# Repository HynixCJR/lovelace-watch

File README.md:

# lovelace watch

this is the repo for lovelace, a smart-ish watch in a thin, compact body. it has:

- four 3x5 led matrices to display the time
- 28 argb leds along the ring of the watch (for flashlight and notification purposes)
- bluetooth 6.0 connection to a smartphone 
- lra vibration motor for notifications
- step tracking
- raise to wake
- auto brightness
- compass
- usb-c charging

this repo currently houses the pcb for the watch.

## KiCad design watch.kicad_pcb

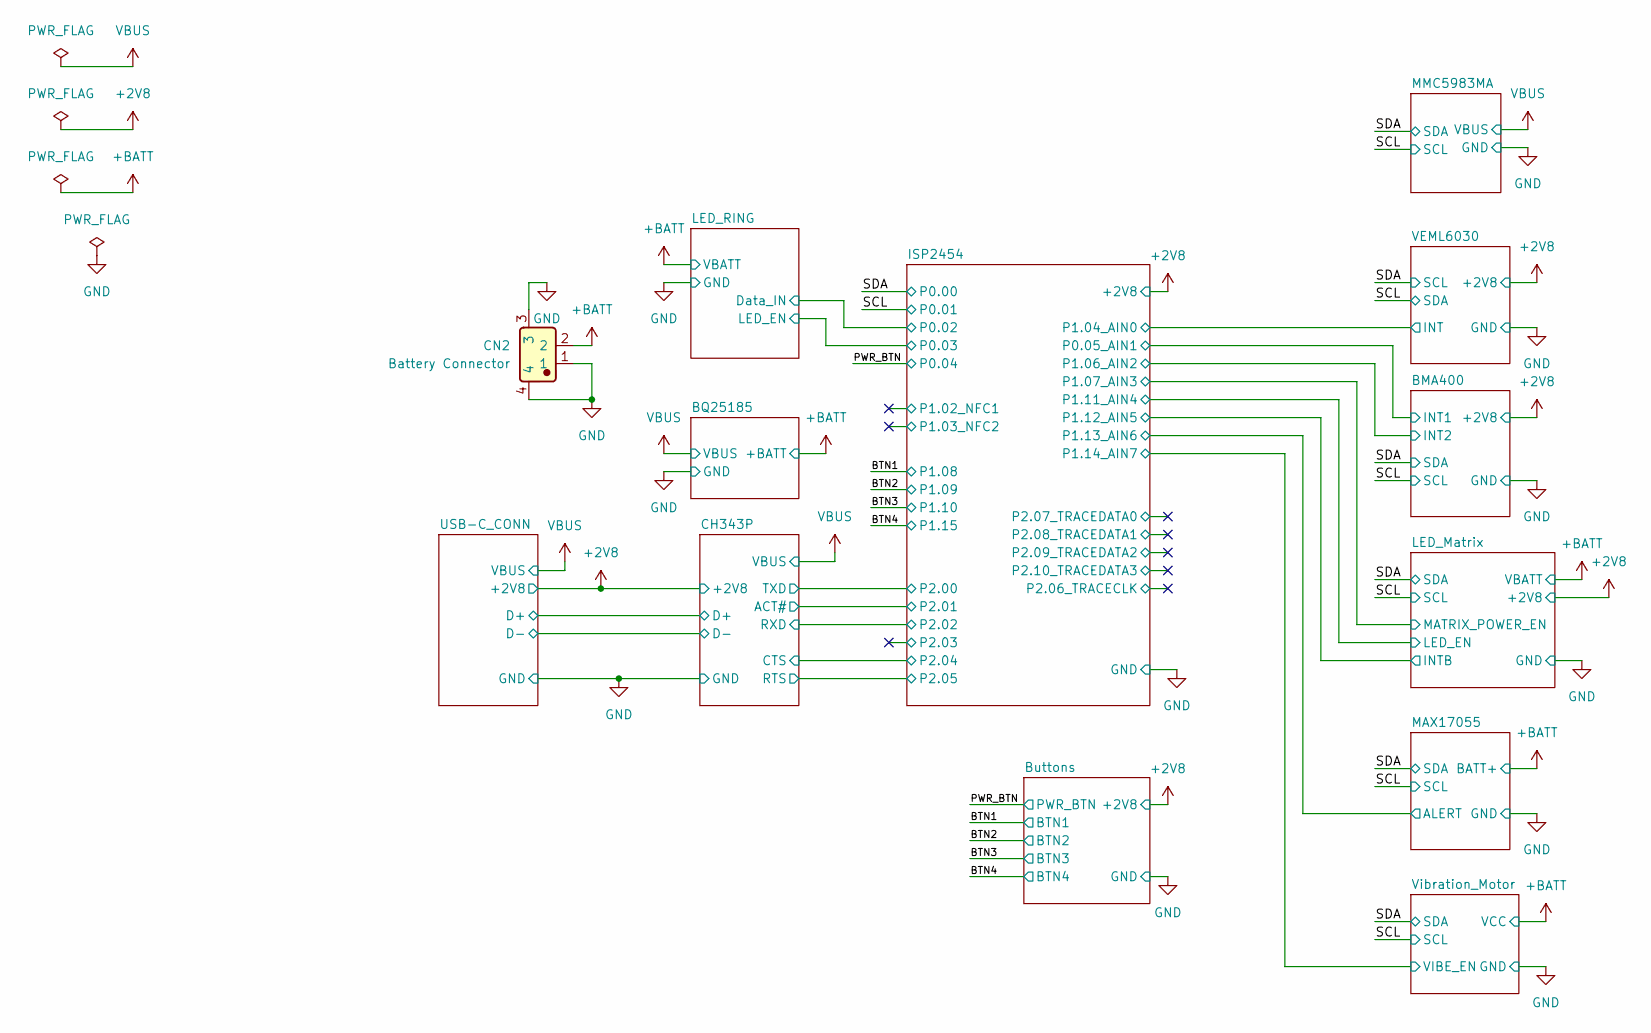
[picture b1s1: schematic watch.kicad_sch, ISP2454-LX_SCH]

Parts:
CN2: Battery Connector; 7900-02A4-TG; Manufacturer Part 7900-02A4-TG; LCSC C53403918

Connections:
+BATT: CN2.2; also elsewhere on the board
GND: CN2.1, CN2.3, CN2.4; also elsewhere on the board

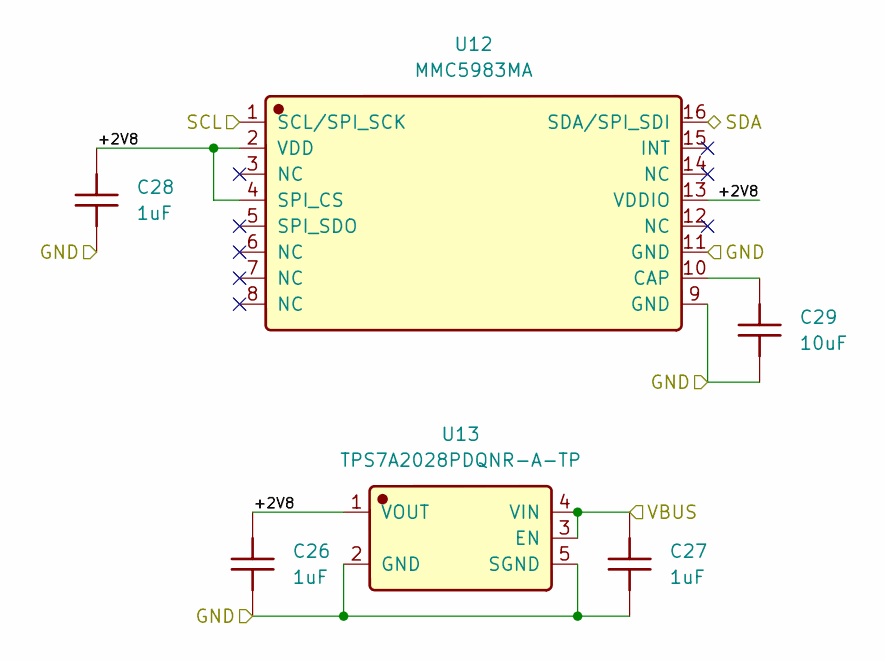
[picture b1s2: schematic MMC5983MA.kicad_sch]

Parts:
C26, C27, C28: 1uF; C_0402_1005Metric; Manufacturer Part 2F01MC105B2K5D0; LCSC C54824955
C29: 10uF; C_0603_1608Metric; Manufacturer Part CL10A106MQ8NNNC; LCSC C1691
U12: MMC5983MA; LGA-16_3x3mm_P0.5mm; Manufacturer Part MMC5983MA; LCSC C404329
U13: TPS7A2028PDQNR-A-TP; UDFN-4-1EP_1x1mm_P0.65mm_EP0.48x0.48mm; Manufacturer Part TPS7A2028PDQNR-A-TP; LCSC C55191366

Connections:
/MMC5983MA/+2V8: C26.2, C28.2, U12.2 (VDD), U12.4 (SPI_CS), U12.13 (VDDIO), U13.1 (VOUT)
/SCL: U12.1 (SCL/SPI_SCK); also elsewhere on the board
/SDA: U12.16 (SDA/SPI_SDI); also elsewhere on the board
GND: C26.1, C27.1, C28.1, C29.1, U12.9 (GND), U12.11 (GND), U13.2 (GND), U13.5 (SGND); also elsewhere on the board
unnamed: C29.2, U12.10 (CAP)
VBUS: C27.2, U13.3 (EN), U13.4 (VIN); also elsewhere on the board

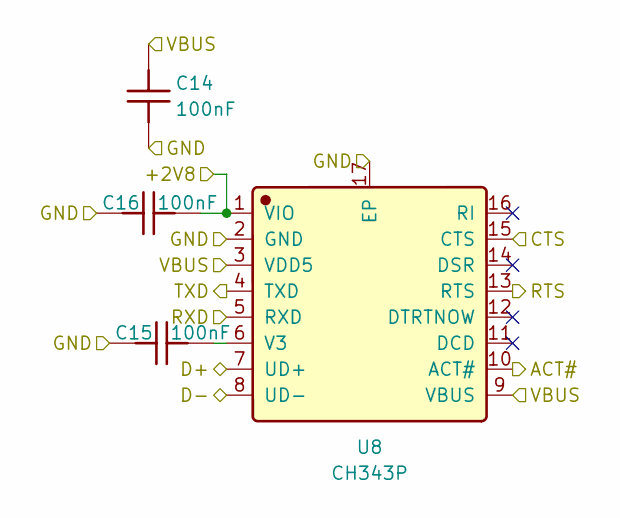
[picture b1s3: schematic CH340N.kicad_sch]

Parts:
C14, C15, C16: 100nF; C_0402_1005Metric; Manufacturer Part 2F01MC104X2K7D0; LCSC C54824947
U8: CH343P; TQFN-16-1EP_3x3mm_P0.5mm_EP1.6x1.6mm; Manufacturer Part CH343P; LCSC C2846043

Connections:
+2V8: C16.1, U8.1 (VIO); also elsewhere on the board
/CH343P/ACT#: U8.10 (ACT#); also elsewhere on the board
/CH343P/CTS: U8.15 (CTS); also elsewhere on the board
/CH343P/D+: U8.7 (UD+); also elsewhere on the board
/CH343P/D-: U8.8 (UD-); also elsewhere on the board
/CH343P/RTS: U8.13 (RTS); also elsewhere on the board
/CH343P/RXD: U8.5 (RXD); also elsewhere on the board
/CH343P/TXD: U8.4 (TXD); also elsewhere on the board
GND: C14.1, C15.2, C16.2, U8.2 (GND), U8.17 (EP); also elsewhere on the board
unnamed: C15.1, U8.6 (V3)
VBUS: C14.2, U8.3 (VDD5), U8.9 (VBUS); also elsewhere on the board

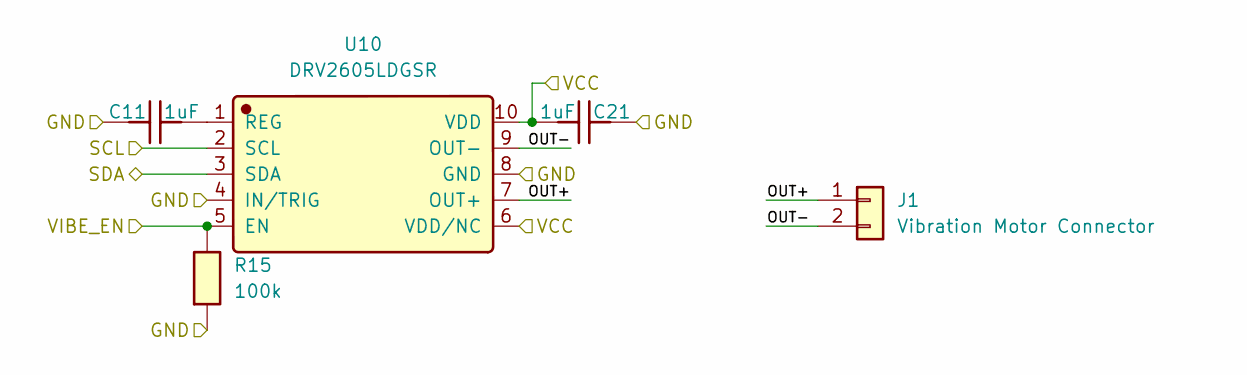
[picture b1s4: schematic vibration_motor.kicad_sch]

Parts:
C11, C21: 1uF; C_0402_1005Metric; Manufacturer Part 2F01MC105B2K5D0; LCSC C54824955
J1: Vibration Motor Connector; Molex_KK-254_AE-6410-02A_1x02_P2.54mm_Vertical
R15: 100k; R_0402_1005Metric; Manufacturer Part HRC0402J104 DNTO; LCSC C54920715
U10: DRV2605LDGSR; MSOP-10_3x3mm_P0.5mm; Manufacturer Part DRV2605LDGSR; LCSC C527464

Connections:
+BATT: C21.1, U10.6 (VDD/NC), U10.10 (VDD); also elsewhere on the board
/ISP2454/P1.14_AIN7: R15.2, U10.5 (EN); also elsewhere on the board
/SCL: U10.2 (SCL); also elsewhere on the board
/SDA: U10.3 (SDA); also elsewhere on the board
/Vibration_Motor/OUT+: J1.1, U10.7 (OUT+)
/Vibration_Motor/OUT-: J1.2, U10.9 (OUT-)
GND: C11.2, C21.2, R15.1, U10.4 (IN/TRIG), U10.8 (GND); also elsewhere on the board
unnamed: C11.1, U10.1 (REG)

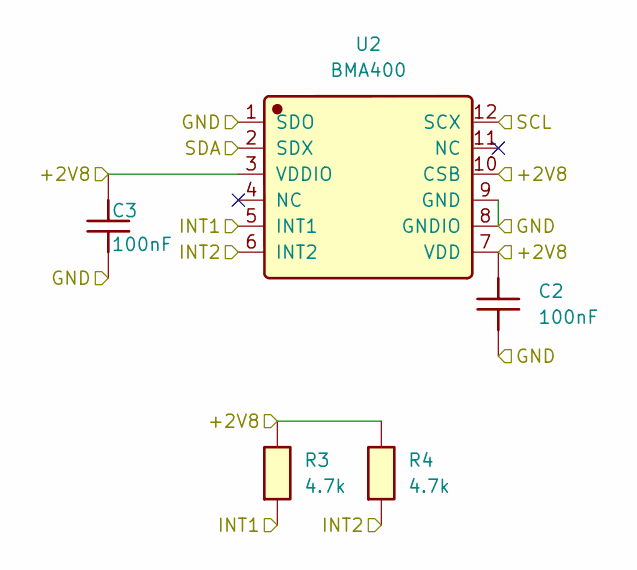
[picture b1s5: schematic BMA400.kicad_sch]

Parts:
C2, C3: 100nF; C_0402_1005Metric; Manufacturer Part 2F01MC104X2K7D0; LCSC C54824947
R3, R4: 4.7k; R_0402_1005Metric; Manufacturer Part RCA024K7JLF; LCSC C22369185
U2: BMA400; LGA-12_2x2mm_P0.5mm; Manufacturer Part BMA400; LCSC C437655

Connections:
+2V8: C2.2, C3.2, R3.2, R4.2, U2.3 (VDDIO), U2.7 (VDD), U2.10 (CSB); also elsewhere on the board
/BMA400/INT1: R3.1, U2.5 (INT1); also elsewhere on the board
/BMA400/INT2: R4.1, U2.6 (INT2); also elsewhere on the board
/SCL: U2.12 (SCX); also elsewhere on the board
/SDA: U2.2 (SDX); also elsewhere on the board
GND: C2.1, C3.1, U2.1 (SDO), U2.8 (GNDIO), U2.9 (GND); also elsewhere on the board

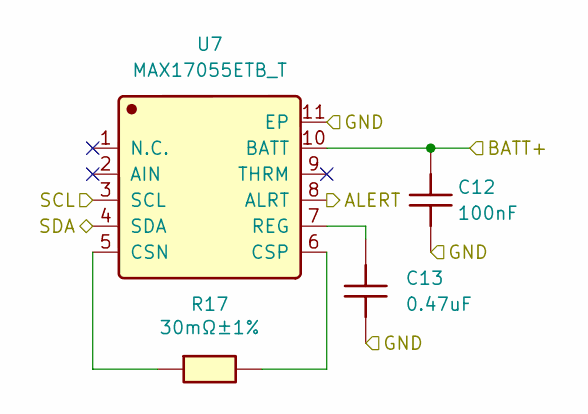
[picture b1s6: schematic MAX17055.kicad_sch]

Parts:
C12: 100nF; C_0402_1005Metric; Manufacturer Part 2F01MC104X2K7D0; LCSC C54824947
C13: 0.47uF; C_0402_1005Metric; Manufacturer Part TCC0402X5R474Z6R3AT; LCSC C48986251
R17: 30mΩ±1%; R_0603_1608Metric; Manufacturer Part RBL06FTR030; LCSC C911682
U7: MAX17055ETB_T; Manufacturer Part MAX17055ETB+T; LCSC C2976422

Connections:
+BATT: C12.2, U7.10 (BATT); also elsewhere on the board
/ISP2454/P1.13_AIN6: U7.8 (ALRT); also elsewhere on the board
/SCL: U7.3 (SCL); also elsewhere on the board
/SDA: U7.4 (SDA); also elsewhere on the board
GND: C12.1, C13.1, U7.11 (EP); also elsewhere on the board
unnamed: R17.1, U7.5 (CSN)
unnamed: R17.2, U7.6 (CSP)
unnamed: C13.2, U7.7 (REG)

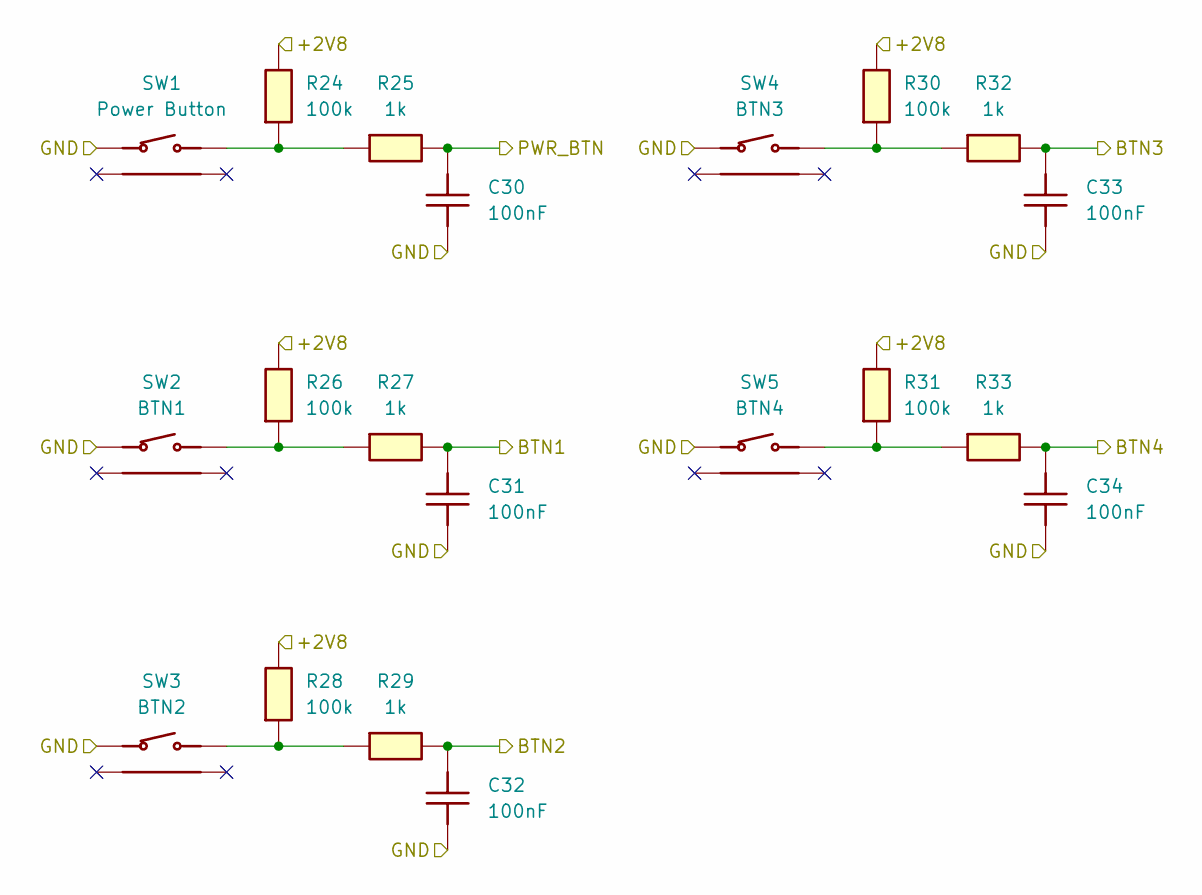
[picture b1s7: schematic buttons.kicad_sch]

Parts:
C30, C31, C32, C33, C34: 100nF; C_0402_1005Metric; Manufacturer Part 2F01MC104X2K7D0; LCSC C54824947
R24, R26, R28, R30, R31: 100k; R_0402_1005Metric; Manufacturer Part HRC0402J104 DNTO; LCSC C54920715
R25, R27, R29, R32, R33: 1k; R_0402_1005Metric; Manufacturer Part CR0402J1K00Q10Z; LCSC C881213
SW1: Power Button; LXTD-0204-034; Manufacturer Part LXTD-0204-034; LCSC C7498205
SW2: BTN1; LXTD-0204-034; Manufacturer Part LXTD-0204-034; LCSC C7498205
SW3: BTN2; LXTD-0204-034; Manufacturer Part LXTD-0204-034; LCSC C7498205
SW4: BTN3; LXTD-0204-034; Manufacturer Part LXTD-0204-034; LCSC C7498205
SW5: BTN4; LXTD-0204-034; Manufacturer Part LXTD-0204-034; LCSC C7498205

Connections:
+2V8: R24.2, R26.2, R28.2, R30.2, R31.2; also elsewhere on the board
/BTN1: C31.2, R27.2; also elsewhere on the board
/BTN2: C32.2, R29.2; also elsewhere on the board
/BTN3: C33.2, R32.2; also elsewhere on the board
/BTN4: C34.2, R33.2; also elsewhere on the board
/PWR_BTN: C30.2, R25.2; also elsewhere on the board
GND: C30.1, C31.1, C32.1, C33.1, C34.1, SW1.1, SW2.1, SW3.1, SW4.1, SW5.1; also elsewhere on the board
unnamed: R24.1, R25.1, SW1.2
unnamed: R26.1, R27.1, SW2.2
unnamed: R28.1, R29.1, SW3.2
unnamed: R30.1, R32.1, SW4.2
unnamed: R31.1, R33.1, SW5.2

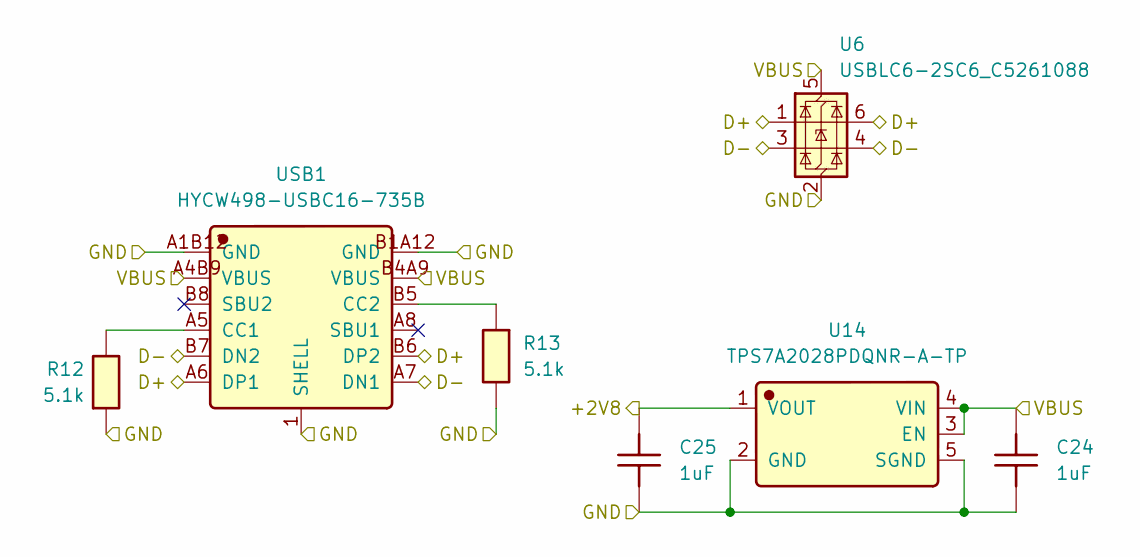
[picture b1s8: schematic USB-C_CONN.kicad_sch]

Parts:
C24, C25: 1uF; C_0402_1005Metric; Manufacturer Part 2F01MC105B2K5D0; LCSC C54824955
R12, R13: 5.1k; R_0402_1005Metric; Manufacturer Part HRC0402F5101DNTO; LCSC C54920691
U6: USBLC6-2SC6_C5261088; SOT-23-6; Manufacturer Part USBLC6-2SC6; LCSC C5261088
U14: TPS7A2028PDQNR-A-TP; UDFN-4-1EP_1x1mm_P0.65mm_EP0.48x0.48mm; Manufacturer Part TPS7A2028PDQNR-A-TP; LCSC C55191366
USB1: HYCW498-USBC16-735B; Manufacturer Part HYCW498-USBC16-735B; LCSC C42400252

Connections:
+2V8: C25.2, U14.1 (VOUT); also elsewhere on the board
/CH343P/D+: U6.1 (I/O1), U6.6 (I/O1), USB1.A6 (DP1), USB1.B6 (DP2); also elsewhere on the board
/CH343P/D-: U6.3 (I/O2), U6.4 (I/O2), USB1.A7 (DN1), USB1.B7 (DN2); also elsewhere on the board
GND: C24.1, C25.1, R12.1, R13.2, U6.2 (GND), U14.2 (GND), U14.5 (SGND), USB1.1 (SHELL), USB1.A1B12 (GND), USB1.B1A12 (GND); also elsewhere on the board
unnamed: R12.2, USB1.A5 (CC1)
unnamed: R13.1, USB1.B5 (CC2)
VBUS: C24.2, U6.5 (VBUS), U14.3 (EN), U14.4 (VIN), USB1.A4B9 (VBUS), USB1.B4A9 (VBUS); also elsewhere on the board

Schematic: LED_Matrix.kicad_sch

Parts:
C4, C6: 100nF; C_0402_1005Metric; Manufacturer Part 2F01MC104X2K7D0; LCSC C54824947
C5: 1uF; C_0402_1005Metric; Manufacturer Part 2F01MC105B2K5D0; LCSC C54824955
C7: 220nF; C_0402_1005Metric; Manufacturer Part TCC0402X7R224K100AT; LCSC C5142574
C8: 10uF; C_0402_1005Metric; Manufacturer Part CGA0402X5R106M100GT; LCSC C6119763
C9, C17: 22uF; C_0402_1005Metric; Manufacturer Part HGC0402R5226M6R3NTEJ; LCSC C7432764
L1: 1uH; PIM201608S1R0MBCA; Manufacturer Part PIM201608S1R0MBCA; LCSC C53514733
LED1, LED2, LED3, LED4, LED5, LED6, LED7, LED8, LED9, LED10, LED11, LED12, LED13, LED14, LED15, LED16, LED17, LED18, LED19, LED20, LED21, LED22, LED23, LED24, LED25, LED26, LED27, LED28, LED29, LED30, LED31, LED32, LED33, LED34, LED35, LED36, LED37, LED38, LED39, LED40, LED41, LED42, LED43, LED44, LED45, LED46, LED47, LED48, LED49, LED50, LED51, LED52, LED53, LED54, LED55, LED56, LED57, LED58, LED59, LED60, LED61, LED62: CT-1005UNWC-P4-D; LED_01005_0402Metric; Manufacturer Part CT-1005UNWC-P4-D; LCSC C54741550
R1: 732k; R_0402_1005Metric; Manufacturer Part FRC0402F7323TS; LCSC C5159692
R5: 4.7k; R_0402_1005Metric; Manufacturer Part RCA024K7JLF; LCSC C22369185
R8, R10, R11: 100k; R_0402_1005Metric; Manufacturer Part HRC0402J104 DNTO; LCSC C54920715
R9: 20k; R_0402_1005Metric; Manufacturer Part HRC0402J203 DNTO; LCSC C54920753
U3: IS31FL3731-QFLS2-TR; QFN-28-1EP_4x4mm_P0.4mm_EP2.3x2.3mm; Manufacturer Part IS31FL3731-QFLS2-TR; LCSC C191206
U4: TPS61023DRLR; MPS_VSON-6_1x1.5mm_P0.5mm; Manufacturer Part TPS61023DRLR; LCSC C919459

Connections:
+2V8: R5.2; also elsewhere on the board
+BATT: C8.2, L1.1, U4.3 (VIN); also elsewhere on the board
/ISP2454/P1.07_AIN3: R10.2, U4.2 (EN); also elsewhere on the board
/ISP2454/P1.11_AIN4: R8.2, U3.3 (SDB); also elsewhere on the board
/ISP2454/P1.12_AIN5: R5.1, U3.4 (INTB); also elsewhere on the board
/LED_Matrix/+5V: C4.2, C5.2, C9.2, C17.2, R1.1, U3.2 (VCC), U4.6 (VOUT)
/LED_Matrix/CA1: LED1.1 (C), LED2.1 (C), LED3.1 (C), LED4.1 (C), LED5.1 (C), LED6.1 (C), LED7.1 (C), LED8.1 (C), LED9.2 (A), LED17.2 (A), LED25.2 (A), LED33.2 (A), LED41.2 (A), LED49.2 (A), LED57.2 (A), U3.21 (CA1)
/LED_Matrix/CA2: LED1.2 (A), LED9.1 (C), LED10.1 (C), LED11.1 (C), LED12.1 (C), LED13.1 (C), LED14.1 (C), LED15.1 (C), LED16.1 (C), LED18.2 (A), LED26.2 (A), LED34.2 (A), LED42.2 (A), LED50.2 (A), LED58.2 (A), U3.22 (CA2)
/LED_Matrix/CA3: LED2.2 (A), LED10.2 (A), LED17.1 (C), LED18.1 (C), LED19.1 (C), LED20.1 (C), LED21.1 (C), LED22.1 (C), LED23.1 (C), LED24.1 (C), LED27.2 (A), LED35.2 (A), LED43.2 (A), LED51.2 (A), LED59.2 (A), U3.23 (CA3)
/LED_Matrix/CA4: LED3.2 (A), LED11.2 (A), LED19.2 (A), LED25.1 (C), LED26.1 (C), LED27.1 (C), LED28.1 (C), LED29.1 (C), LED30.1 (C), LED31.1 (C), LED32.1 (C), LED36.2 (A), LED44.2 (A), LED52.2 (A), LED60.2 (A), U3.24 (CA4)
/LED_Matrix/CA5: LED4.2 (A), LED12.2 (A), LED20.2 (A), LED28.2 (A), LED33.1 (C), LED34.1 (C), LED35.1 (C), LED36.1 (C), LED37.1 (C), LED38.1 (C), LED39.1 (C), LED40.1 (C), LED45.2 (A), LED53.2 (A), LED61.2 (A), U3.25 (CA5)
/LED_Matrix/CA6: LED5.2 (A), LED13.2 (A), LED21.2 (A), LED29.2 (A), LED37.2 (A), LED41.1 (C), LED42.1 (C), LED43.1 (C), LED44.1 (C), LED45.1 (C), LED46.1 (C), LED47.1 (C), LED48.1 (C), LED54.2 (A), LED62.2 (A), U3.26 (CA6)
/LED_Matrix/CA7: LED6.2 (A), LED14.2 (A), LED22.2 (A), LED30.2 (A), LED38.2 (A), LED46.2 (A), LED49.1 (C), LED50.1 (C), LED51.1 (C), LED52.1 (C), LED53.1 (C), LED54.1 (C), LED55.1 (C), LED56.1 (C), U3.27 (CA7)
/LED_Matrix/CA8: LED7.2 (A), LED15.2 (A), LED23.2 (A), LED31.2 (A), LED39.2 (A), LED47.2 (A), LED55.2 (A), LED57.1 (C), LED58.1 (C), LED59.1 (C), LED60.1 (C), LED61.1 (C), LED62.1 (C), U3.28 (CA8)
/LED_Matrix/CA9: LED8.2 (A), LED16.2 (A), LED24.2 (A), LED32.2 (A), LED40.2 (A), LED48.2 (A), LED56.2 (A), U3.1 (CA9)
/LED_Matrix/CB1: U3.7 (CB1)
/LED_Matrix/CB2: U3.8 (CB2)
/LED_Matrix/CB3: U3.9 (CB3)
/LED_Matrix/CB4: U3.10 (CB4)
/LED_Matrix/CB5: U3.11 (CB5)
/LED_Matrix/CB6: U3.12 (CB6)
/LED_Matrix/CB7: U3.13 (CB7)
/LED_Matrix/CB8: U3.14 (CB8)
/LED_Matrix/CB9: U3.15 (CB9)
/SCL: U3.20 (SCL); also elsewhere on the board
/SDA: U3.19 (SDA); also elsewhere on the board
GND: C4.1, C5.1, C6.1, C7.1, C8.1, C9.1, C17.1, R8.1, R9.2, R10.1, R11.2, U3.5 (GND), U3.18 (AD), U3.29 (EP), U4.4 (GND); also elsewhere on the board
unnamed: C6.2, U3.16 (C_FILT)
unnamed: C7.2, U3.17 (IN)
unnamed: R9.1, U3.6 (R-EXT)
unnamed: R1.2, R11.1, U4.1 (FB)
unnamed: L1.2, U4.5 (SW)

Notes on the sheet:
220nF used for audio, maybe remove?
LEDs need >3V so IS31FL3731 takes in VCC=5V, and TPS61023 boosts VBATT to 5V. LED_MATRIX_EN must be pulled up by nRF54 to enable the LED matrix, otherwise it cuts power.
Place decoupling capacitors close to VCC pin

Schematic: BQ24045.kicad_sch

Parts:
C10, C19: 1uF; C_0402_1005Metric; Manufacturer Part 2F01MC105B2K5D0; LCSC C54824955
C18: 10uF; C_0402_1005Metric; Manufacturer Part CGA0402X5R106M100GT; LCSC C6119763
R2: 3k; R_0402_1005Metric; Manufacturer Part GR0402J3KTAG00; LCSC C49653053
R18, R20: 10k; R_0402_1005Metric; Manufacturer Part HRC0402J103 DNTO; LCSC C54920717
R19: 43k; R_0402_1005Metric; Manufacturer Part HRC0402J433 DNTO; LCSC C54920800
U9: BQ25185DLHR; Texas_DLH0010A_WSON-10-1EP_2.2x2mm_P0.4mm_EP0.9x1.5mm; Manufacturer Part BQ25185DLHR; LCSC C19725033

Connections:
+BATT: C19.1, U9.2 (BAT); also elsewhere on the board
GND: C10.2, C18.1, C19.2, R2.2, R18.1, R19.2, R20.1, U9.5 (GND), U9.11 (EP); also elsewhere on the board
unnamed: R18.2, U9.4 (CE#)
unnamed: R19.1, U9.7 (ILIM/VSET)
unnamed: R2.1, U9.8 (ISET)
unnamed: C18.2, U9.1 (SYS)
unnamed: R20.2, U9.6 (TS/MR)
VBUS: C10.1, U9.10 (IN); also elsewhere on the board

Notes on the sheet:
100mA charge limit
NTC not used

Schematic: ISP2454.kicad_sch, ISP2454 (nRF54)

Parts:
C1: 10uF; C_0402_1005Metric; Manufacturer Part CGA0402X5R106M100GT; LCSC C6119763
J2: SWD Programming Header; PinHeader_1x05_P2.54mm_Vertical
R6, R7: 4.7k; R_0402_1005Metric; Manufacturer Part RCA024K7JLF; LCSC C22369185
U1: ISP2454; MANUFACTURER PN ISP2454-LX

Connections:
+2V8: C1.1, J2.1, R6.2, R7.2, U1.26 (VCC_nRF); also elsewhere on the board
/BMA400/INT1: U1.38 (P1_05_AIN1); also elsewhere on the board
/BMA400/INT2: U1.35 (P1_06_AIN2); also elsewhere on the board
/BTN1: U1.19 (P1_08); also elsewhere on the board
/BTN2: U1.39 (P1_09); also elsewhere on the board
/BTN3: U1.10 (P1_10); also elsewhere on the board
/BTN4: U1.17 (P1_15); also elsewhere on the board
/CH343P/ACT#: U1.6 (P2_01); also elsewhere on the board
/CH343P/CTS: U1.44 (P2_04); also elsewhere on the board
/CH343P/RTS: U1.42 (P2_05); also elsewhere on the board
/CH343P/RXD: U1.46 (P2_02); also elsewhere on the board
/CH343P/TXD: U1.47 (P2_00); also elsewhere on the board
/ISP2454/MOD+ANT: U1.20 (OUT_ANT), U1.22 (OUT_MOD)
/ISP2454/P0.02: U1.32 (P0_02); also elsewhere on the board
/ISP2454/P0.03: U1.34 (P0.03); also elsewhere on the board
/ISP2454/P1.02_NFC1: U1.2 (P1_02_NFC1)
/ISP2454/P1.03_NFC2: U1.4 (P1_03_NFC2)
/ISP2454/P1.04_AIN0: U1.40 (P1_04_AIN0); also elsewhere on the board
/ISP2454/P1.07_AIN3: U1.36 (P1_07_AIN3); also elsewhere on the board
/ISP2454/P1.11_AIN4: U1.48 (P1_11_AIN4); also elsewhere on the board
/ISP2454/P1.12_AIN5: U1.43 (P1_12_AIN5); also elsewhere on the board
/ISP2454/P1.13_AIN6: U1.41 (P1_13_AIN6); also elsewhere on the board
/ISP2454/P1.14_AIN7: U1.45 (P1_14_AIN7); also elsewhere on the board
/ISP2454/P2.03: U1.3 (P2_03)
/ISP2454/P2.06_TRACECLK: U1.15 (P2_06_TRACELK)
/ISP2454/P2.07_TRACEDATA0: U1.11 (P2_07_TRACEDATA0)
/ISP2454/P2.08_TRACEDATA1: U1.9 (P2_08_TRACEDATA1)
/ISP2454/P2.09_TRACEDATA2: U1.37 (P2_09_TRACEDATA2)
/ISP2454/P2.10_TRACEDATA3: U1.5 (P2_10_TRACEDATA3)
/PWR_BTN: U1.33 (P0_04); also elsewhere on the board
/SCL: R6.1, U1.27 (P0_01); also elsewhere on the board
/SDA: R7.1, U1.29 (P0_00); also elsewhere on the board
GND: C1.2, J2.5, U1.1 (VSS), U1.7 (VSS), U1.8 (VSS), U1.12 (VSS), U1.14 (VSS), U1.16 (VSS), U1.18 (VSS), U1.21 (VSS), U1.23 (VSS), U1.24 (VSS), U1.25 (VSS), U1.31 (VSS); also elsewhere on the board
unnamed: J2.2, U1.30 (SWDCLK)
unnamed: J2.3, U1.28 (SWDIO)
unnamed: J2.4, U1.13 (nRESET)

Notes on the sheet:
used for I2C
Analog capable GPIO
Pin 20 connected to Pin 22 for Normal Operation

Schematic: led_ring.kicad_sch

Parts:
C22, C23: 22uF; C_0402_1005Metric; Manufacturer Part HGC0402R5226M6R3NTEJ; LCSC C7432764
L2: 470nH; PIM201608S1R0MBCA; Manufacturer Part PIM201612SR47MBCA; LCSC C53514771
LED65, LED72, LED79, LED86: WS2812B-2020-V6; Manufacturer Part WS2812B-2020-V6; LCSC C52917434
LED66, LED67, LED68, LED69, LED70, LED71, LED73, LED74, LED75, LED76, LED77, LED78, LED80, LED81, LED82, LED83, LED84, LED85, LED87, LED88, LED89, LED90, LED91, LED92: WS2812B-1313-V6; Manufacturer Part WS2812B-1313-V6; LCSC C52941388
R16, R23: 100k; R_0402_1005Metric; Manufacturer Part HRC0402J104 DNTO; LCSC C54920715
R21: 91k; R_0402_1005Metric; Manufacturer Part HRC0402J913 DNTO; LCSC C54920839
R22: 511k; R_0402_1005Metric; Manufacturer Part FRC0402F5113TS; LCSC C5126239
U11: TPS63802DLAR; VSON-10-1EP_3x3mm_P0.5mm_EP1.2x2mm; Manufacturer Part TPS63802DLAR; LCSC C2845237

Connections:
+BATT: C22.2, U11.10 (VIN); also elsewhere on the board
/ISP2454/P0.02: LED65.3 (DI); also elsewhere on the board
/ISP2454/P0.03: R23.2, U11.1 (EN); also elsewhere on the board
/LED_RING/+3V3: C23.1, LED65.4 (VDD), LED66.1 (VDD), LED67.1 (VDD), LED68.1 (VDD), LED69.1 (VDD), LED70.1 (VDD), LED71.1 (VDD), LED72.4 (VDD), LED73.1 (VDD), LED74.1 (VDD), LED75.1 (VDD), LED76.1 (VDD), LED77.1 (VDD), LED78.1 (VDD), LED79.4 (VDD), LED80.1 (VDD), LED81.1 (VDD), LED82.1 (VDD), LED83.1 (VDD), LED84.1 (VDD), LED85.1 (VDD), LED86.4 (VDD), LED87.1 (VDD), LED88.1 (VDD), LED89.1 (VDD), LED90.1 (VDD), LED91.1 (VDD), LED92.1 (VDD), R16.1, R22.2, U11.6 (VOUT)
GND: C22.1, C23.2, LED65.2 (GND), LED66.3 (GND), LED67.3 (GND), LED68.3 (GND), LED69.3 (GND), LED70.3 (GND), LED71.3 (GND), LED72.2 (GND), LED73.3 (GND), LED74.3 (GND), LED75.3 (GND), LED76.3 (GND), LED77.3 (GND), LED78.3 (GND), LED79.2 (GND), LED80.3 (GND), LED81.3 (GND), LED82.3 (GND), LED83.3 (GND), LED84.3 (GND), LED85.3 (GND), LED86.2 (GND), LED87.3 (GND), LED88.3 (GND), LED89.3 (GND), LED90.3 (GND), LED91.3 (GND), LED92.3 (GND), R21.2, R23.1, U11.2 (MODE), U11.3 (AGND), U11.8 (GND); also elsewhere on the board
unnamed: LED65.1 (DO), LED66.4 (DIN)
unnamed: LED66.2 (DOUT), LED67.4 (DIN)
unnamed: LED67.2 (DOUT), LED68.4 (DIN)
unnamed: LED68.2 (DOUT), LED69.4 (DIN)
unnamed: LED69.2 (DOUT), LED70.4 (DIN)
unnamed: LED70.2 (DOUT), LED71.4 (DIN)
unnamed: LED71.2 (DOUT), LED72.3 (DI)
unnamed: LED72.1 (DO), LED73.4 (DIN)
unnamed: LED73.2 (DOUT), LED74.4 (DIN)
unnamed: LED74.2 (DOUT), LED75.4 (DIN)
unnamed: LED75.2 (DOUT), LED76.4 (DIN)
unnamed: LED76.2 (DOUT), LED77.4 (DIN)
unnamed: LED77.2 (DOUT), LED78.4 (DIN)
unnamed: LED78.2 (DOUT), LED79.3 (DI)
unnamed: LED79.1 (DO), LED80.4 (DIN)
unnamed: LED80.2 (DOUT), LED81.4 (DIN)
unnamed: LED81.2 (DOUT), LED82.4 (DIN)
unnamed: LED82.2 (DOUT), LED83.4 (DIN)
unnamed: LED83.2 (DOUT), LED84.4 (DIN)
unnamed: LED84.2 (DOUT), LED85.4 (DIN)
unnamed: LED85.2 (DOUT), LED86.3 (DI)
unnamed: LED86.1 (DO), LED87.4 (DIN)
unnamed: LED87.2 (DOUT), LED88.4 (DIN)
unnamed: LED88.2 (DOUT), LED89.4 (DIN)
unnamed: LED89.2 (DOUT), LED90.4 (DIN)
unnamed: LED90.2 (DOUT), LED91.4 (DIN)
unnamed: LED91.2 (DOUT), LED92.4 (DIN)
unnamed: R21.1, R22.1, U11.4 (FB)
unnamed: L2.1, U11.9 (L1)
unnamed: L2.2, U11.7 (L2)
unnamed: R16.2, U11.5 (PG)

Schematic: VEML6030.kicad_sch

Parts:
C20: 100nF; C_0402_1005Metric; Manufacturer Part 2F01MC104X2K7D0; LCSC C54824947
R14: 4.7k; R_0402_1005Metric; Manufacturer Part RCA024K7JLF; LCSC C22369185
U5: VEML6030-GS15; Manufacturer Part VEML6030-GS15; LCSC C2655119

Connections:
+2V8: C20.2, R14.2, U5.6 (VDD); also elsewhere on the board
/ISP2454/P1.04_AIN0: R14.1, U5.3 (INT); also elsewhere on the board
/SCL: U5.2 (SDA); also elsewhere on the board
/SDA: U5.5 (SCL); also elsewhere on the board
GND: C20.1, U5.1 (GND), U5.4 (ADDR); also elsewhere on the board

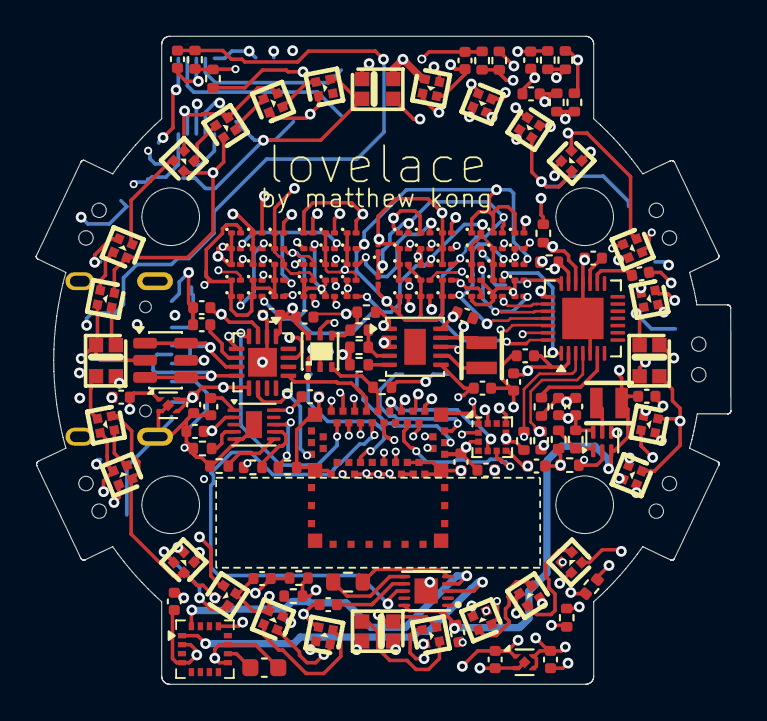
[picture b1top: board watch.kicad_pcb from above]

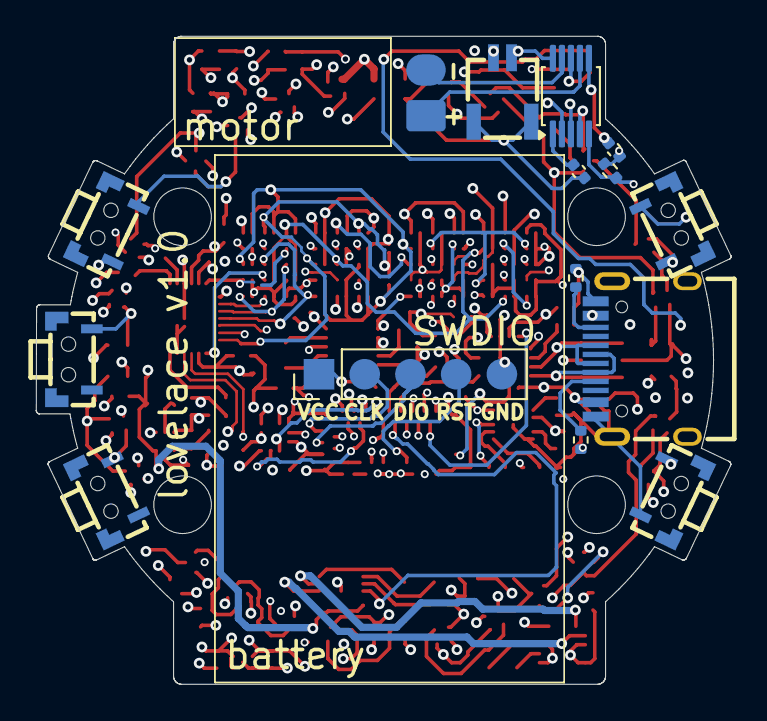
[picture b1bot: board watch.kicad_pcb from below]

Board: 8 copper layers, 38.6 x 36.0 mm, 182 parts (15 on the bottom side), 100 nets.
